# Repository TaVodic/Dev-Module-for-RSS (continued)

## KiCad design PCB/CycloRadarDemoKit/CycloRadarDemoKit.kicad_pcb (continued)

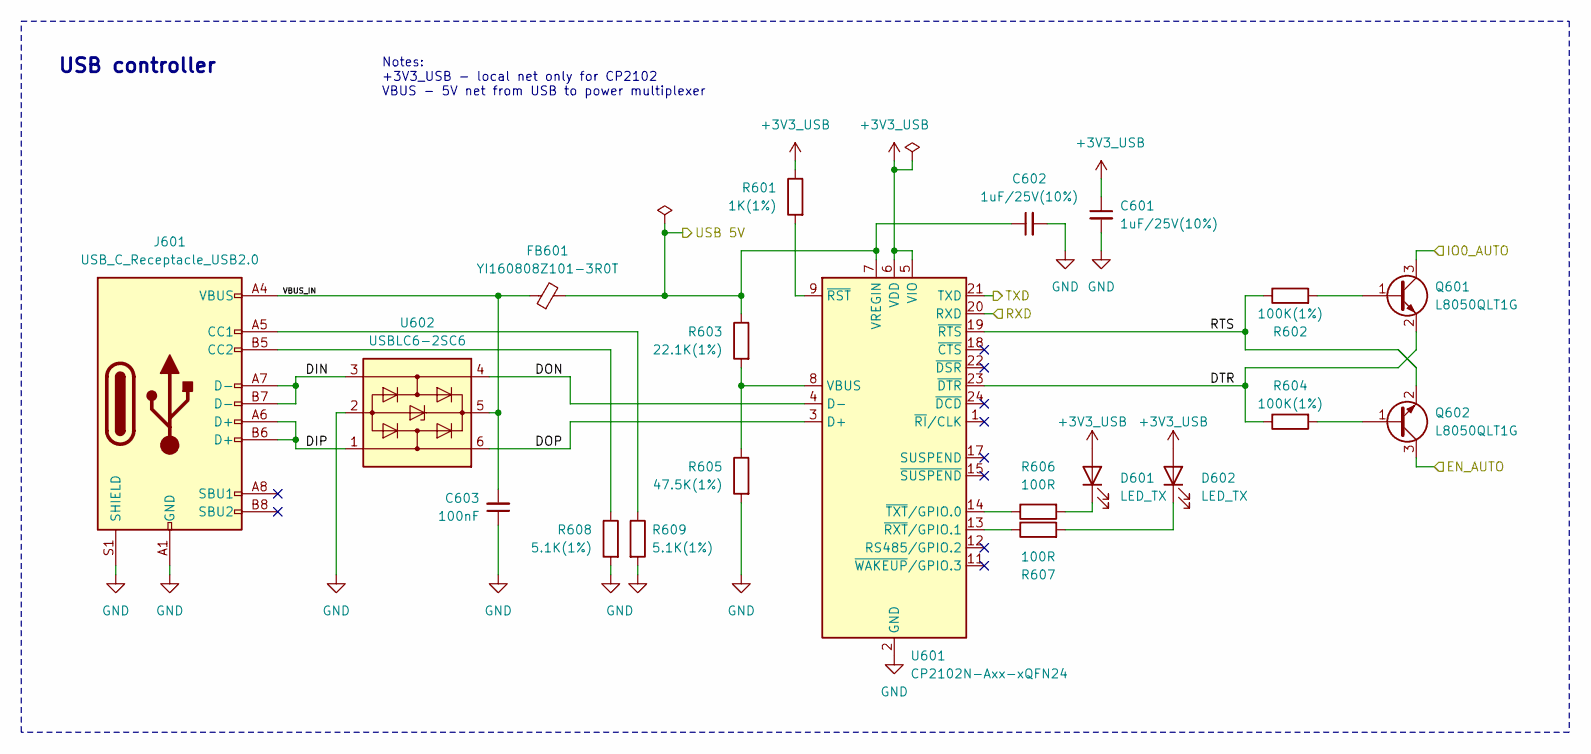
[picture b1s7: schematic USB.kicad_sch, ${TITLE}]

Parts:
C601, C602: 1uF/25V(10%); C_0402_1005Metric; LCSC C52923
C603: 100nF; C_0402_1005Metric
D601, D602: LED_TX; LED_0603_1608Metric; LCSC C3028830
FB601: YI160808Z101-3R0T; R_0603_1608Metric; LCSC C3011210
J601: USB_C_Receptacle_USB2.0; TYPE-C-SMD_YIYUAN_YTC-TC16-273A1; LCSC C5260486
Q601, Q602: L8050QLT1G; SOT-23; LCSC C49581
R601: 1K(1%); R_0603_1608Metric; LCSC C21190
R602, R604: 100K(1%); R_0603_1608Metric; LCSC C25803
R603: 22.1K(1%); R_0603_1608Metric; LCSC C25961
R605: 47.5K(1%); R_0603_1608Metric; LCSC C23061
R606, R607: 100R; R_0603_1608Metric; LCSC C22775
R608, R609: 5.1K(1%); R_0603_1608Metric; LCSC C23186
U601: CP2102N-Axx-xQFN24; QFN-24-1EP_4x4mm_P0.5mm_EP2.6x2.6mm; LCSC C969151
U602: USBLC6-2SC6; SOT-23-6; LCSC C7519

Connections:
+3V3_USB: C601.1, D601.2 (A), D602.2 (A), R601.1, U601.5 (VIO), U601.6 (VDD)
/5V + 3V3/USB 5V: C602.1, FB601.2, R603.1, U601.7 (VREGIN); also elsewhere on the board
/ESP32/EN_AUTO: Q602.3 (C); also elsewhere on the board
/ESP32/IO0_AUTO: Q601.3 (C); also elsewhere on the board
/USB/DIN: J601.A7 (D-), J601.B7 (D-), U602.3 (I/O2)
/USB/DIP: J601.A6 (D+), J601.B6 (D+), U602.1 (I/O1)
/USB/DON: U601.4 (D-), U602.4 (I/O2)
/USB/DOP: U601.3 (D+), U602.6 (I/O1)
/USB/DTR: Q601.2 (E), R604.1, U601.23 (~DTR)
/USB/RTS: Q602.2 (E), R602.1, U601.19 (~RTS)
/USB/RXD: U601.20 (RXD); also elsewhere on the board
/USB/TXD: U601.21 (TXD); also elsewhere on the board
/USB/VBUS_IN: C603.2, FB601.1, J601.A4 (VBUS), J601.A9 (VBUS), J601.B4 (VBUS), J601.B9 (VBUS), U602.5 (VBUS)
GND: C601.2, C602.2, C603.1, J601.A1 (GND), J601.A12 (GND), J601.B1 (GND), J601.B12 (GND), J601.S1 (SHIELD), R605.2, R608.2, R609.2, U601.2 (GND), U601.25 (GND), U602.2 (GND); also elsewhere on the board
unnamed: D601.1 (K), R606.2
unnamed: D602.1 (K), R607.2
unnamed: J601.A5 (CC1), R609.1
unnamed: J601.B5 (CC2), R608.1
unnamed: Q601.1 (B), R602.2
unnamed: Q602.1 (B), R604.2
unnamed: R603.2, R605.1, U601.8 (VBUS)
unnamed: R601.2, U601.9 (~RST)
unnamed: R607.1, U601.13 (~RXT/GPIO.1)
unnamed: R606.1, U601.14 (~TXT/GPIO.0)

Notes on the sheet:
Notes: +3V3_USB - local net only for CP2102 VBUS - 5V net from USB to power multiplexer
USB controller

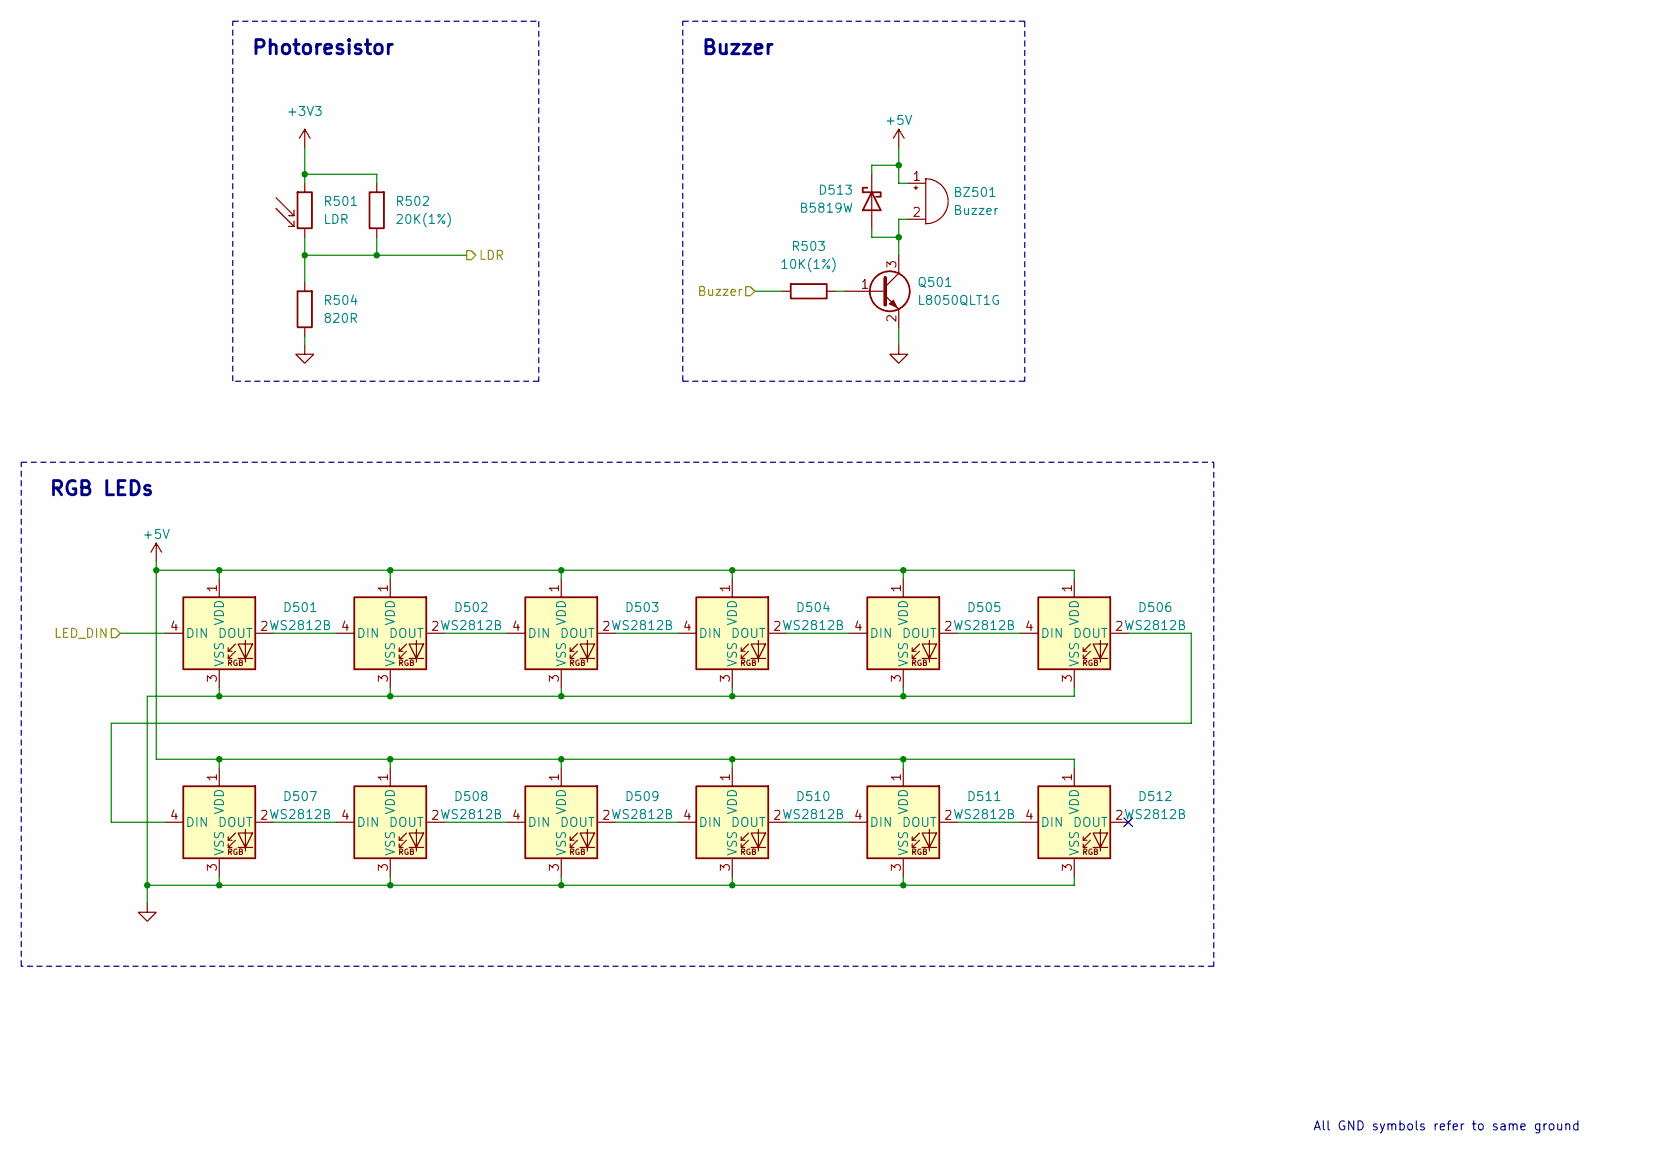
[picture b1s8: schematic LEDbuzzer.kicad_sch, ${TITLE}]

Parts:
BZ501: Buzzer; Buzzer_D9mm_P5mm; Mouser 253-AX905P3
D501, D502, D503, D504, D505, D506, D507, D508, D509, D510, D511, D512: WS2812B; LED_SK6812MINI_PLCC4_3.5x3.5mm_P1.75mm; LCSC C527089
D513: B5819W; D_SOD-123; LCSC C8598
Q501: L8050QLT1G; SOT-23; LCSC C49581
R501: LDR; R_LDR_5.1x4.3mm_P3.4mm_Vertical
R502: 20K(1%); R_0603_1608Metric; LCSC C4184
R503: 10K(1%); R_0603_1608Metric; LCSC C25804
R504: 820R; R_0603_1608Metric; LCSC C23253

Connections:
+3V3: R501.1, R502.2; also elsewhere on the board
+5V: BZ501.1 (-), D501.1 (VDD), D502.1 (VDD), D503.1 (VDD), D504.1 (VDD), D505.1 (VDD), D506.1 (VDD), D507.1 (VDD), D508.1 (VDD), D509.1 (VDD), D510.1 (VDD), D511.1 (VDD), D512.1 (VDD), D513.1 (K); also elsewhere on the board
/ESP32/Buzzer: R503.2; also elsewhere on the board
/ESP32/LED: D501.4 (DIN); also elsewhere on the board
/ESP32/Photo_res: R501.2, R502.1, R504.2; also elsewhere on the board
GND: D501.3 (VSS), D502.3 (VSS), D503.3 (VSS), D504.3 (VSS), D505.3 (VSS), D506.3 (VSS), D507.3 (VSS), D508.3 (VSS), D509.3 (VSS), D510.3 (VSS), D511.3 (VSS), D512.3 (VSS), Q501.2 (E), R504.1; also elsewhere on the board
unnamed: BZ501.2 (+), D513.2 (A), Q501.3 (C)
unnamed: D501.2 (DOUT), D502.4 (DIN)
unnamed: D502.2 (DOUT), D503.4 (DIN)
unnamed: D503.2 (DOUT), D504.4 (DIN)
unnamed: D504.2 (DOUT), D505.4 (DIN)
unnamed: D505.2 (DOUT), D506.4 (DIN)
unnamed: D506.2 (DOUT), D507.4 (DIN)
unnamed: D507.2 (DOUT), D508.4 (DIN)
unnamed: D508.2 (DOUT), D509.4 (DIN)
unnamed: D509.2 (DOUT), D510.4 (DIN)
unnamed: D510.2 (DOUT), D511.4 (DIN)
unnamed: D511.2 (DOUT), D512.4 (DIN)
unnamed: Q501.1 (B), R503.1

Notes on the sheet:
RGB LEDs
All GND symbols refer to same ground
Photoresistor
Buzzer

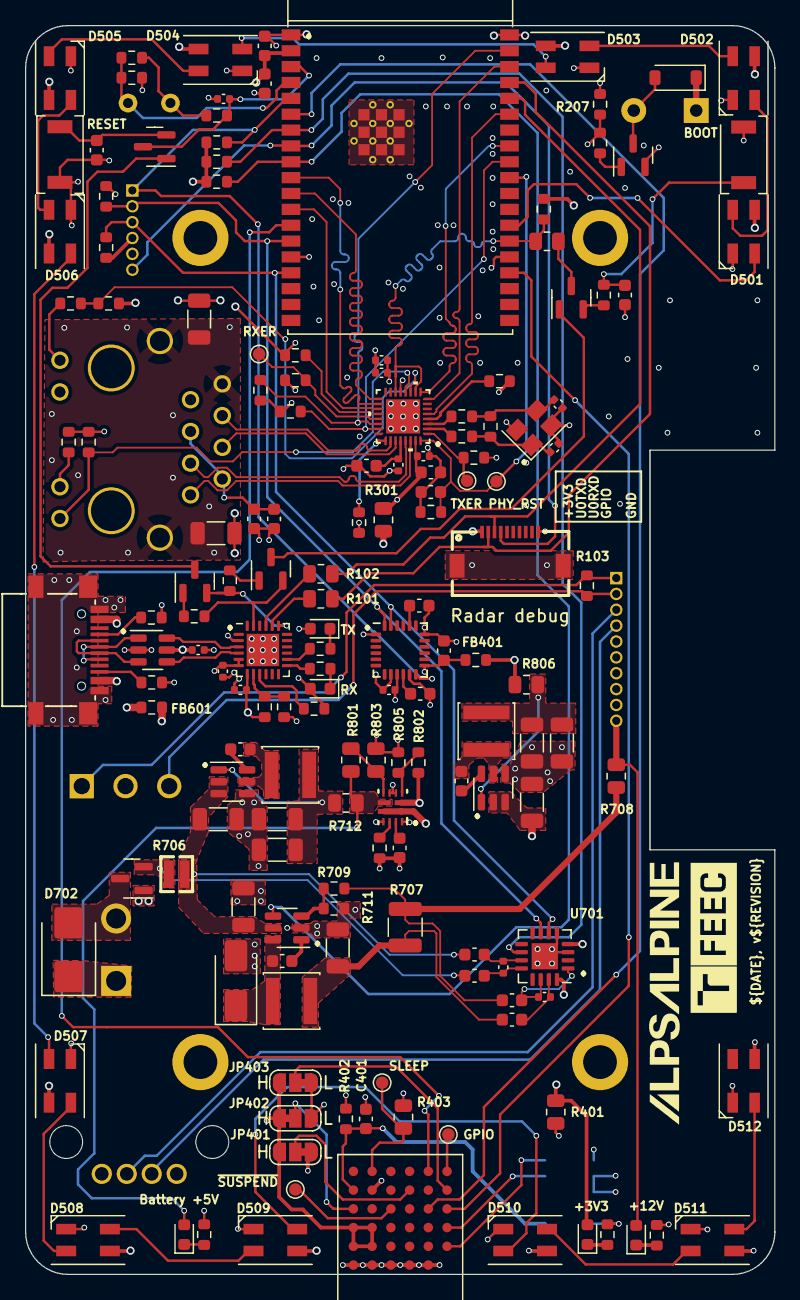
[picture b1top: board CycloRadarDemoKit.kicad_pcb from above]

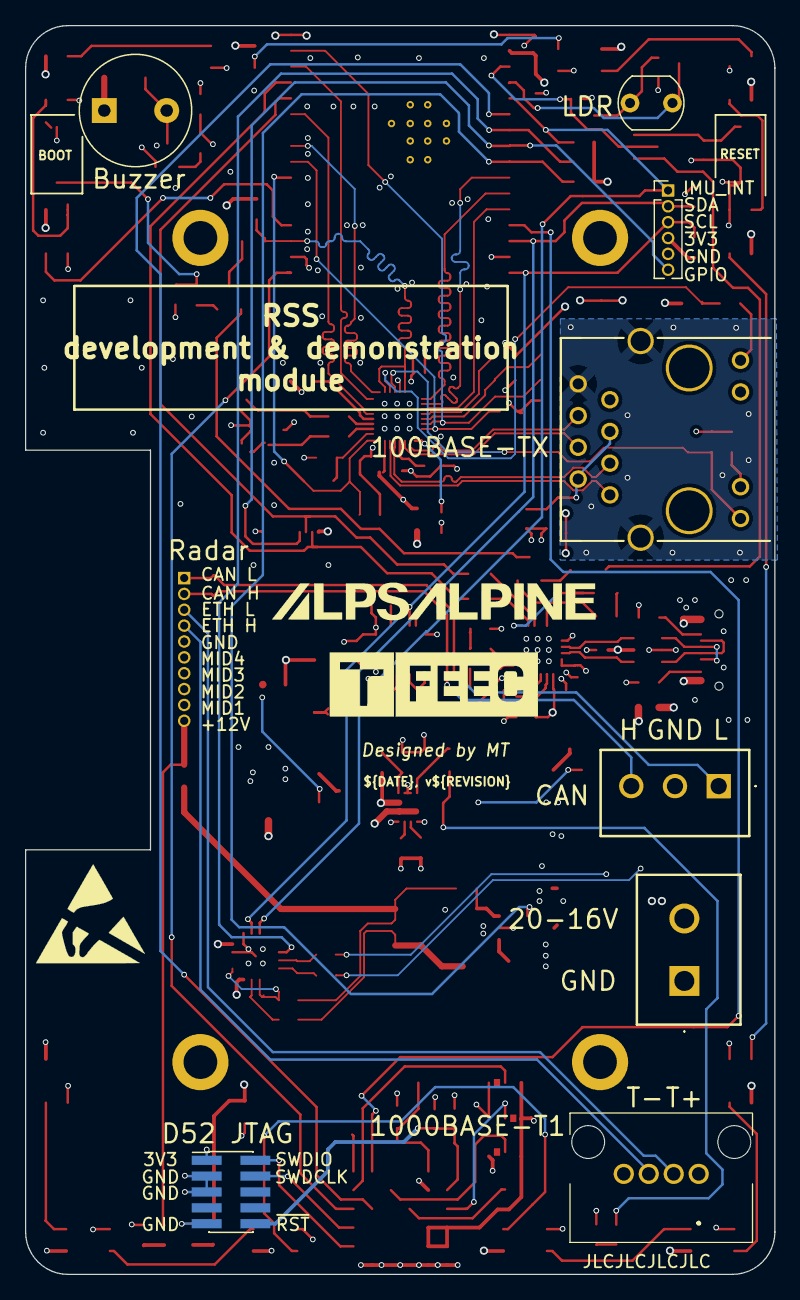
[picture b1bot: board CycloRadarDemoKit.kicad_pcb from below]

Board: 4 copper layers, 60.0 x 100.0 mm, 173 parts (9 on the bottom side), 133 nets.

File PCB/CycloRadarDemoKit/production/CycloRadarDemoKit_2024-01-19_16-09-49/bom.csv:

Designator,Footprint,Quantity,Value,LCSC Part #
BZ501,Buzzer_D9mm_P5mm,1,Buzzer,
"C201, C202",0603,2,10uF,C19702
"C203, C303, C304, C306, C601, C602, C701, C702",0402,8,1uF/25V(10%),C52923
"C204, C205, C301, C310, C311, C403, C404, C706, C801, C802",0603,10,100nF/50V(10%),C14663
"C302, C305, C307, C705, C708, C804",0603,6,10uF/25V(20%),C96446
"C308, C309",0402,2,20pF/50V(5%),C182483
"C312, C313",1206,2,4.7nF/2kV(10%),C41017
C401,0603,1,100nF/50V(10%),DNP
C402,0402,1,10nF/50V(10%),C15195
C405,0603,1,2.2nF/50V(10%),C1604
C703,0603,1,10nF/50V(10%),C57112
"C704, C707, C709, C803, C805",1206,5,22uF/16V(20%),C87162
"D201, D202",SOT-23,2,BAT54A,C283256
"D501, D502, D503, D504, D505, D506, D507, D508, D509, D510, D511, D512",LED_SK6812MINI_PLCC4_3.5x3.5mm_P1.75mm,12,WS2812B,C527089
D513,D_SOD-123,1,B5819W,C8598
"D601, D602",0603,2,LED_TX,C3028830
D603,SOT-143,1,SP0503BAHT,C2682275
D701,0603,1,LED_12V,C284922
D702,D_SMA,1,B230A-13-F,C12889
D703,D_SMB,1,SMBJ20A,C3001979
D704,0603,1,LED_5V,C87326
D801,0603,1,LED_3V3,C497937
"FB401, FB601",0603,2,YI160808Z101-3R0T,C3011210
J101,PinHeader_1x06_P1.27mm_Vertical,1,I2C conn,
J102,PinHeader_1x10_P1.27mm_Vertical,1,Radar pins,
J103,Molex_39501-1003,1,CAN,
J104,Molex_347920040,1,100BASE-T1,
J105,AFC30-S10FCC-00,1,Radar debug,C395235
J301,RJ45_Taoglas_TMJD0012BENL,1,TMJD0012BENL,
J401,PinHeader_2x05_P1.27mm_Vertical_SMD,1,ANT_SWD,DNP
J601,TYPE-C-SMD_YIYUAN_YTC-TC16-273A1,1,USB_C_Receptacle_USB2.0,C5260486
J701,Molex_39521-1002,1,20-16V Supply Voltage,
JP401,SolderJumper-3_P1.3mm_Bridged12_RoundedPad1.0x1.5mm_NumberLabels,1,BR1,
JP402,SolderJumper-3_P1.3mm_Bridged12_RoundedPad1.0x1.5mm_NumberLabels,1,BR2,
JP403,SolderJumper-3_P1.3mm_Bridged12_RoundedPad1.0x1.5mm_NumberLabels,1,BR3,
L701,L_Changjiang_FNR4018S,1,15uH/1A,C167809
"L702, L801",L_Sunlord_SWPA4020S,2,4.7uH/2.85A,C98363
"Q501, Q601, Q602",SOT-23,3,L8050QLT1G,C49581
Q701,SOT-23,1,SI2309CDS,C3021112
"R101, R102, R301, R505, R708, R712, R801, R806",0805,8,0R,C17477
R103,0603,1,120,DNP
R201,0603,1,20K(5%),C4184
"R202, R203, R204, R307, R503, R701, R805",0603,7,10K(1%),C25804
"R205, R206",0603,2,4.7K,C23162
"R207, R402",0603,2,10K(1%),DNP
"R208, R601",0603,2,1K(1%),C21190
"R302, R303, R304, R305, R306, R309, R315, R608, R609",0603,9,5.1K(1%),C23186
R308,0603,1,6.19K(1%),C403300
"R310, R314",0603,2,0R,C21189
R311,0603,1,270R,C22966
R312,0603,1,1M(1%),DNP
R313,0603,1,220R,C22962
"R401, R403",0805,2,0R,DNP
R501,R_LDR_5.1x4.3mm_P3.4mm_Vertical,1,LDR,
R502,0603,1,20K(1%),C4184
R504,0603,1,820R,C23253
"R602, R604",0603,2,100K(1%),C25803
R603,0603,1,22.1K(1%),C25961
R605,0603,1,47.5K(1%),C23061
"R606, R607",0603,2,100R,C22775
"R702, R703, R704, R705",0603,4,10R(1%),C22859
R706,1210,1,0.16R(5%),C175910
R707,1210,1,0.3R(5%),C175910
R709,0603,1,51K(1%),C23196
"R710, R713",0603,2,2K,C22764
R711,0603,1,3.6K(1%),C22980
R802,0603,1,1.1K(1%),C22764
R803,0805,1,NC,DNP
R804,0603,1,47k(1%),C25819
R807,0603,1,200R,C8218
SW201,SW_SPST_TS-1088R,1,RESET,C455280
SW202,SW_SPST_TS-1088R,1,BOOT MODE,C455280
TP301,TestPoint_Pad_D1.0mm,1,RESET,
TP302,TestPoint_Pad_D1.0mm,1,TXER,
TP303,TestPoint_Pad_D1.0mm,1,RXER,
TP401,TestPoint_Pad_D1.0mm,1,SLEEP,
TP402,TestPoint_Pad_D1.0mm,1,~{SUSPEND},
TP403,TestPoint_Pad_D1.0mm,1,GPIO,
U101,ALPS_USRR5_woPins,1,~,
U201,ESP32-WROVER-E_ThermalVias,1,ESP32-WROVER-E-N16R8,C529589
U301,QFN_IP101GRI_WIZ,1,IP101GRI,C703537
U401,Garmin_M8-35_9.8x14.0mm_Layout6x6_P1.5mm,1,D52MxxM8,DNP
U402,InvenSense_QFN-24_4x4mm_P0.5mm,1,MPU-6050,C24112
U601,QFN-24-1EP_4x4mm_P0.5mm_EP2.6x2.6mm,1,CP2102N-Axx-xQFN24,C964632
U701,Texas_RGV_S-PVQFN-N16_EP2.1x2.1mm,1,INA3221,C181255
U702,TSOT-23-6,1,RT8259,C425775
U703,TSOT-23-6,1,AP63205WU,C2071056
U801,TPS2121,1,TPS2121RUXR,C485916
U802,TSOT-23-6,1,AP63203WU,C780769
Y301,Crystal_SMD_3225-4Pin_3.2x2.5mm,1,25MHz,C3003239

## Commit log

2023-10-03 ESP32 S2 Blink test PlatformIO
2023-10-03 readme edited
2023-10-09 Added assignment and gitignore
2023-10-09 Readme
2023-10-09 removed first project
2023-10-17 overleaf link
2023-10-17 CP added to Readme
2023-10-20 working int32 subscriber
2023-10-20 .gitignore updated
2023-10-20 deleted branch merge
2023-10-24 thesis link new
2023-10-24 2. meeting prep
2023-10-24 after meeting
2023-11-14 reorganization of folder
2023-11-14 readme power management
2023-11-14 DC/DC suggestion
2023-11-16 PM ICs choosed
2023-11-16 PCB PHY WIP_1
2023-11-18 .gitignore changed
2023-11-18 PCB WIP Started working on CP2102
2023-11-19 USB designed with TODOs, ESP part changed
2023-11-20 Readme, PCB new symbol routed
2023-11-21 PCB power manag. WIP
2023-11-23 Power management almost done
    5V/3.3V changed to AP63203
2023-11-24 RJ45 chose, leds connected
2023-11-27 RJ45 footprint added
2023-11-27 LED strip default example
2023-11-27 LED strip staticaly working
2023-11-28 MCU routed, two GPIO tested
2023-12-01 MPU added, power managemennt updated
2023-12-03 added buzzer and pins for Radar
2023-12-03 more components fthprnt added
2023-12-03 added more LCSC parts
2023-12-04 PCB ready for review
2023-12-05 PCB after review
2023-12-17 schematic cosmetics, power management diagram upgrated
2023-12-19 Schematic edited, split sheets
    improved PM diagram
2023-12-19 starting the mockup
2023-12-19 PCB mockup, grid repaired
2023-12-19 layout mockup done
2023-12-20 PCB, 3Dmodel
    mockup PCB version done, schcematic exported to latex, 3D model generated and exported to latex
2023-12-27 sortingAbbr, cosmetics schematic, export schematic to thesis
2024-01-04 PCB small updates, schemtatic cosmetics, SEP FINAL
2024-01-04 buzzer 3D repaired
2024-01-06 UART tested
2024-01-10 All peripherals checked, changed ESP32 pinout
2024-01-10 PCB holes moved, PCB rounded, 3d model mock-up
2024-01-17 PCB before aperture change
2024-01-17 PCB edited, 3D case mock-up
2024-01-17 reanotated schematic, routing started
2024-01-18 LEDs reodered, connectors moved
2024-01-18 Parts ordered on PCB, 1206->0803 10uF, 0803->0402 1uF
2024-01-18 RMII routed, first try
2024-01-18 PCB upper part almost routed
2024-01-19 PCB upper part ready for review
2024-01-19 starting USB
2024-01-19 PCB grid origin repaired
2024-01-19 USB layout, long traces from upper prepaired
2024-01-19 production/ removed
2024-01-20 DC/DC routed, stuckup properties changed
    ready for PCB resize
2024-01-20 parts moved, ready to move
2024-01-20 PCB resized 60x100mm
2024-01-21 DC/DC placement, conn-s swaped
2024-01-21 Creo 3D design upload (backup)
2024-01-22 PCB routing done
2024-01-22 PCB and 3D ready for review
2024-01-22 silkscreen repaired
2024-01-23 Logos added
2024-01-23 start of repair after review
2024-01-24 Review changes WIP, USB ESD changed, MDIC pullup added
2024-01-25 ready for 2. review
2024-01-28 PCB finished and reviewed
2024-01-29 JLCPCB mistakes repaired, cosmetics on PCB
2024-01-29 Sematic Versioning implemented, whish list added
2024-02-07 schematic note added
2024-02-23 Writing and routing notes updated
2024-02-23 readme updated
2024-02-28 plug conn added to Wishlist.xlsx
2024-03-04 3D PCB renewed
2024-03-07 initial development added
2024-03-07 photos added, readme rewrited
2024-03-09 3D model updated for EEICT
2024-03-09 reverted kicad_pro, the frame was corrupted
2024-03-09 KiCad project updated to KiCad v8.0.0
2024-03-09 v1.0.0 visuals added
2024-03-09 EEICT article added
2024-03-09 removed sensitive files 1
2024-03-09 sensitive files removed 2
2024-03-09 writing notes removed
2024-03-09 Radovan's notes implemented to EEICT paper
